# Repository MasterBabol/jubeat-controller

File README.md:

# jubeat-controller
jubeat controller: 4x4 acrylic gamepad  (recovered)

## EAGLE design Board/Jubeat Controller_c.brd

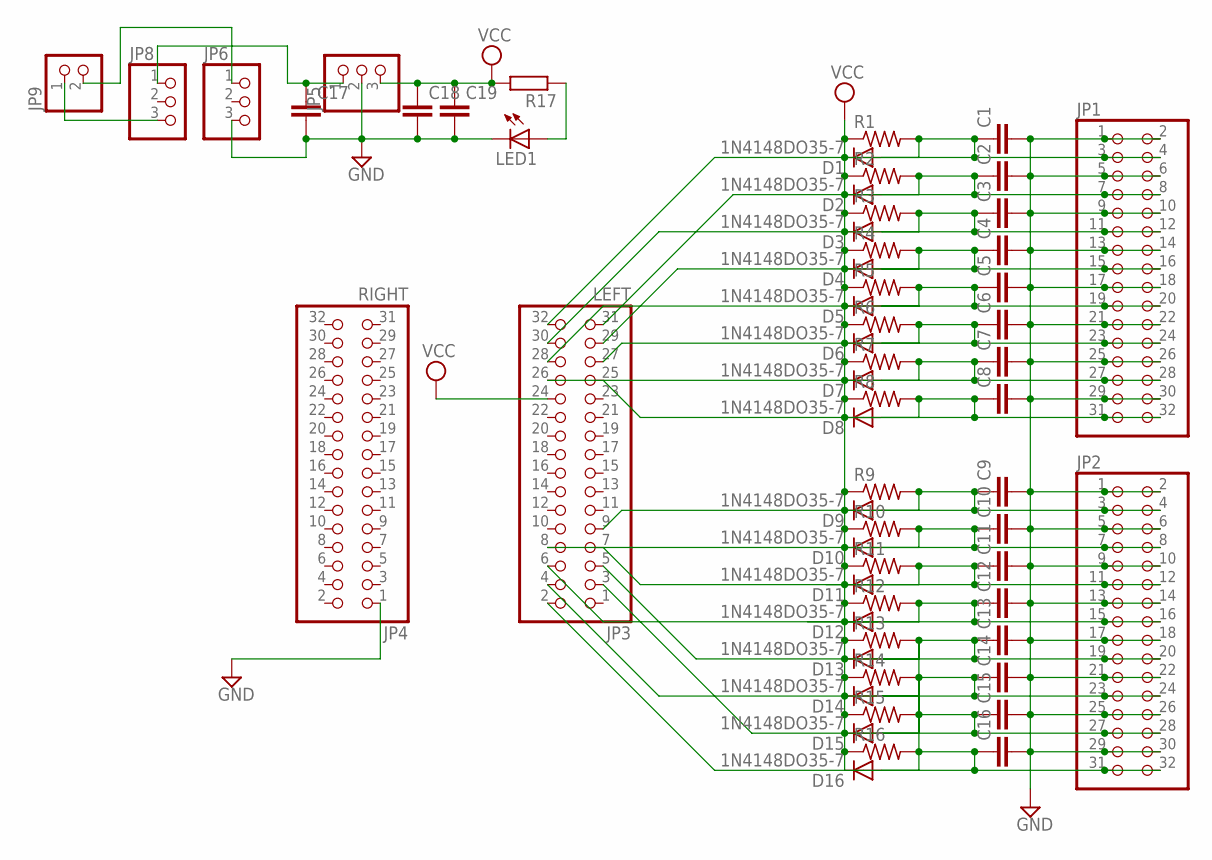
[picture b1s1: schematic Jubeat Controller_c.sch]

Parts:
C1, C2, C3, C4, C5, C6, C7, C8, C9, C10, C11, C12, C13, C14, C15, C16, C17, C18, C19: C-EU050-025X075; C050-025X075
D1, D2, D3, D4, D5, D6, D7, D8, D9, D10, D11, D12, D13, D14, D15, D16: 1N4148DO35-7; DO35-7
JP1, JP2: PINHD-2X16; 2X16
JP3: LEFT; 2X16
JP4: RIGHT; 2X16
JP5, JP6, JP8: PINHD-1X3; 1X03
JP9: PINHD-1X2; 1X02
LED1: LED5MM
R1, R2, R3, R4, R5, R6, R7, R8, R9, R10, R11, R12, R13, R14, R15, R16: R-US_0207/7; 0207/7
R17: R-EU_0207/7; 0207/7

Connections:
GND: C1.2, C2.2, C3.2, C4.2, C5.2, C6.2, C7.2, C8.2, C9.2, C10.2, C11.2, C12.2, C13.2, C14.2, C15.2, C16.2, C17.2, C18.2, C19.2, JP1.1, JP1.2, JP1.5, JP1.6, JP1.9, JP1.10, JP1.13, JP1.14, JP1.17, JP1.18, JP1.21, JP1.22, JP1.25, JP1.26, JP1.29, JP1.30, JP2.1, JP2.2, JP2.5, JP2.6, JP2.9, JP2.10, JP2.13, JP2.14, JP2.17, JP2.18, JP2.21, JP2.22, JP2.25, JP2.26, JP2.29, JP2.30, JP4.1, JP5.2, JP6.3, LED1.K (C)
unnamed: C17.1, JP5.1, JP8.1
unnamed: C2.1, D2.A, JP1.7, JP1.8, JP3.31, R2.2
unnamed: JP6.1, JP9.2
unnamed: C6.1, D6.A, JP1.23, JP1.24, JP3.27, R6.2
unnamed: LED1.A, R17.1
unnamed: C8.1, D8.A, JP1.31, JP1.32, JP3.25, R8.2
unnamed: C9.1, D9.A, JP2.3, JP2.4, JP3.9, R9.2
unnamed: C10.1, D10.A, JP2.7, JP2.8, JP3.8, R10.2
unnamed: C11.1, D11.A, JP2.11, JP2.12, JP3.7, R11.2
unnamed: C12.1, D12.A, JP2.15, JP2.16, JP3.6, R12.2
unnamed: C13.1, D13.A, JP2.19, JP2.20, JP3.5, R13.2
unnamed: C14.1, D14.A, JP2.23, JP2.24, JP3.4, R14.2
unnamed: C15.1, D15.A, JP2.27, JP2.28, JP3.3, R15.2
unnamed: C16.1, D16.A, JP2.31, JP2.32, JP3.2, R16.2
unnamed: C7.1, D7.A, JP1.27, JP1.28, JP3.26, R7.2
unnamed: JP8.3, JP9.1
unnamed: C5.1, D5.A, JP1.19, JP1.20, JP3.28, R5.2
unnamed: C3.1, D3.A, JP1.11, JP1.12, JP3.30, R3.2
unnamed: C1.1, D1.A, JP1.3, JP1.4, JP3.32, R1.2
unnamed: C4.1, D4.A, JP1.15, JP1.16, JP3.29, R4.2
VCC: C18.1, C19.1, D1.C, D2.C, D3.C, D4.C, D5.C, D6.C, D7.C, D8.C, D9.C, D10.C, D11.C, D12.C, D13.C, D14.C, D15.C, D16.C, JP3.24, JP5.3, R1.1, R2.1, R3.1, R4.1, R5.1, R6.1, R7.1, R8.1, R9.1, R10.1, R11.1, R12.1, R13.1, R14.1, R15.1, R16.1, R17.2

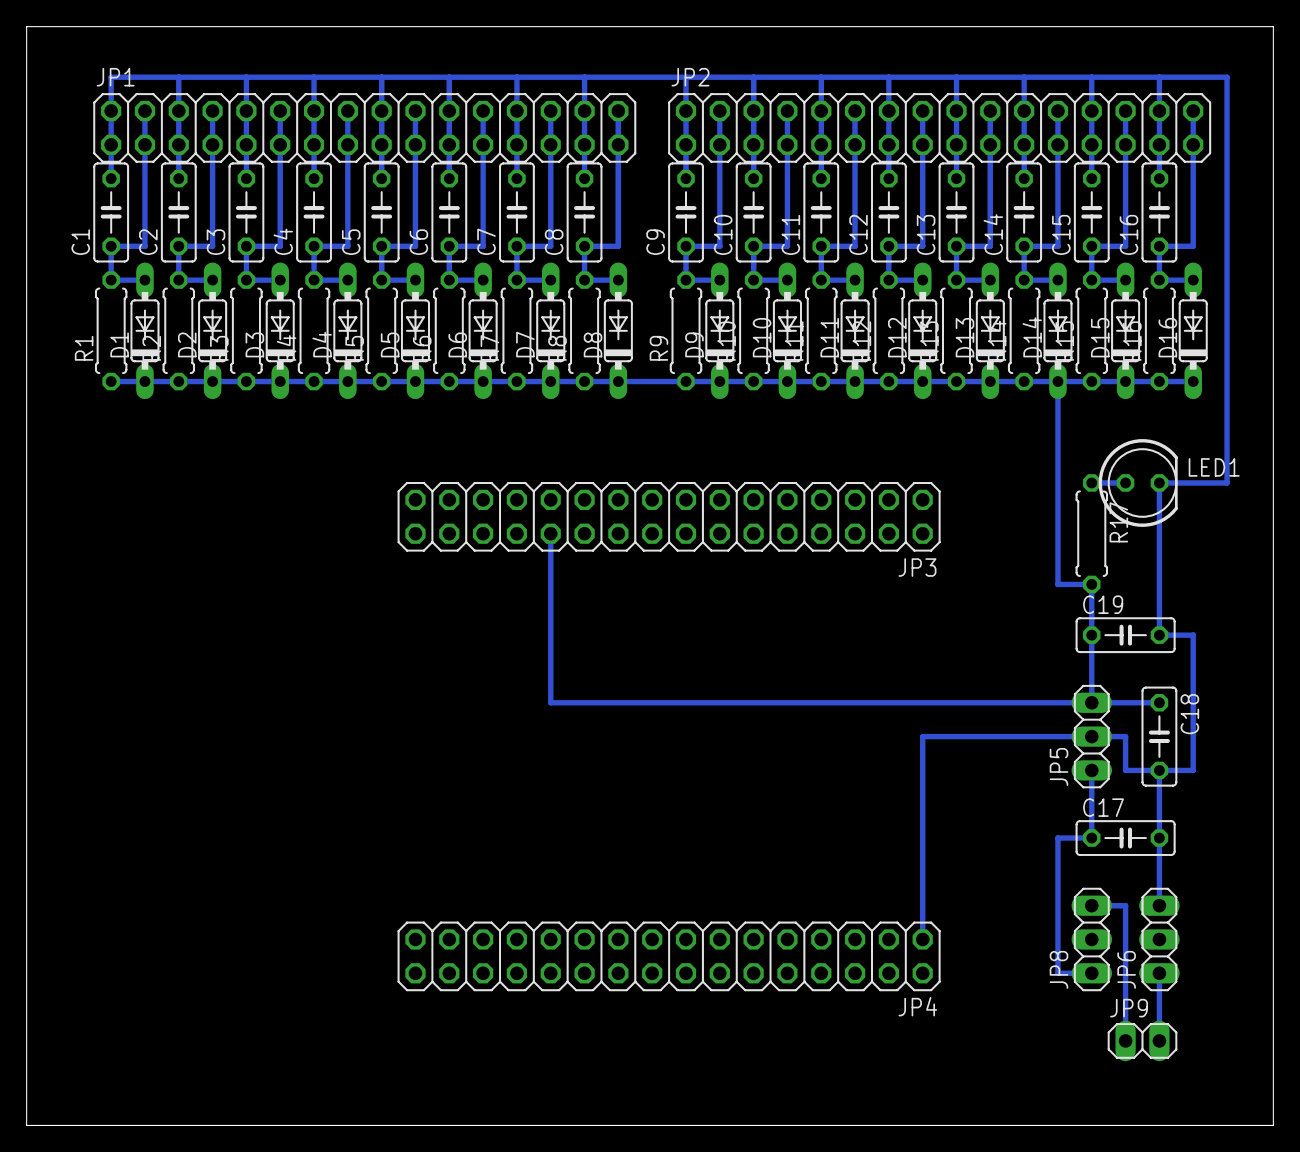
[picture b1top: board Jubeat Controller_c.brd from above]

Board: 2 copper layers, 93.7 x 82.5 mm, 61 parts (0 on the bottom side), 22 nets.

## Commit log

2019-10-13 Recover excavated files
